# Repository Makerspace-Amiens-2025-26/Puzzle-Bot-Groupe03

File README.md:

# Puzzle Bot

## Description

Puzzle Bot est une machine automatisée capable de détecter, saisir et assembler les pièces d'un puzzle. Le projet combine plusieurs domaines techniques : conception mécanique, électronique, programmation, vision par ordinateur et fabrication numérique.

## Objectifs
* Détecter les pièces d'un puzzle à l'aide d'une caméra.
* Identifier leur position et leur orientation.
* Déplacer les pièces grâce à un système robotisé.
* Assembler automatiquement le puzzle.
## Technologies utilisées
* Arduino
* Python
* OpenCV
* Onshape
* Impression 3D 
* Découpe laser
## Structure du projet 
* /CAO : modèles 3D et plans.
* /Code : programmes de contrôle et de vision.
* /Electronique : schémas et câblage.
* /Documentation : rapports, poster et ressources.
## Équipe
* Moutassi joseph 
* Mbognie Donna
* Fokem bracins
* Antoni calvin
* Andy Metogo
* Elsy Kounda
## Ressources
* Documentation du projet
* Modèle Onshape
* Poster de présentation

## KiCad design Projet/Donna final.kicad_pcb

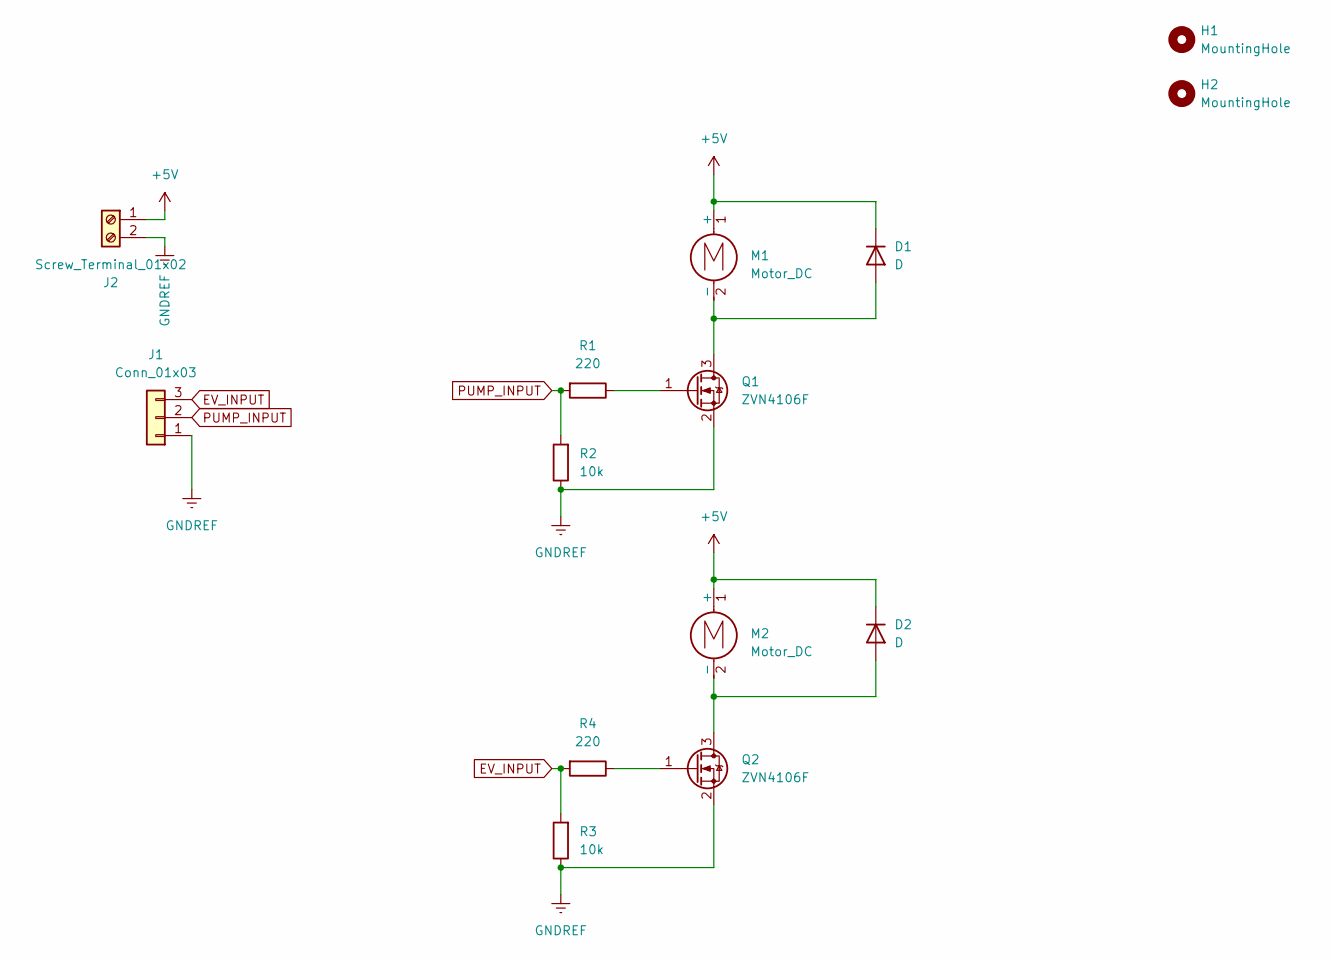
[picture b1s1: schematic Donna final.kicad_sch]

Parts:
D1, D2: D; D_SMA
H1, H2: MountingHole; MountingHole_3.2mm_M3
J1: Conn_01x03; PinHeader_1x03_P2.54mm_Vertical
J2: Screw_Terminal_01x02; TerminalBlock_Phoenix_PT-1,5-2-5.0-H_1x02_P5.00mm_Horizontal
M1, M2: Motor_DC; TerminalBlock_Phoenix_PT-1,5-2-5.0-H_1x02_P5.00mm_Horizontal
Q1, Q2: ZVN4106F; TO-92L_Inline
R1, R4: 220; R_1206_3216Metric_Pad1.30x1.75mm_HandSolder
R2, R3: 10k; R_1206_3216Metric_Pad1.30x1.75mm_HandSolder

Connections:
+5V: D1.1 (K), D2.1 (K), J2.1, M1.1 (+), M2.1 (+)
EV_INPUT: J1.3, R3.2, R4.2
GNDREF: J1.1, J2.2, Q1.2 (S), Q2.2 (S), R2.1, R3.1
unnamed: D1.2 (A), M1.2 (-), Q1.3 (D)
unnamed: D2.2 (A), M2.2 (-), Q2.3 (D)
unnamed: Q1.1 (G), R1.1
unnamed: Q2.1 (G), R4.1
PUMP_INPUT: J1.2, R1.2, R2.2

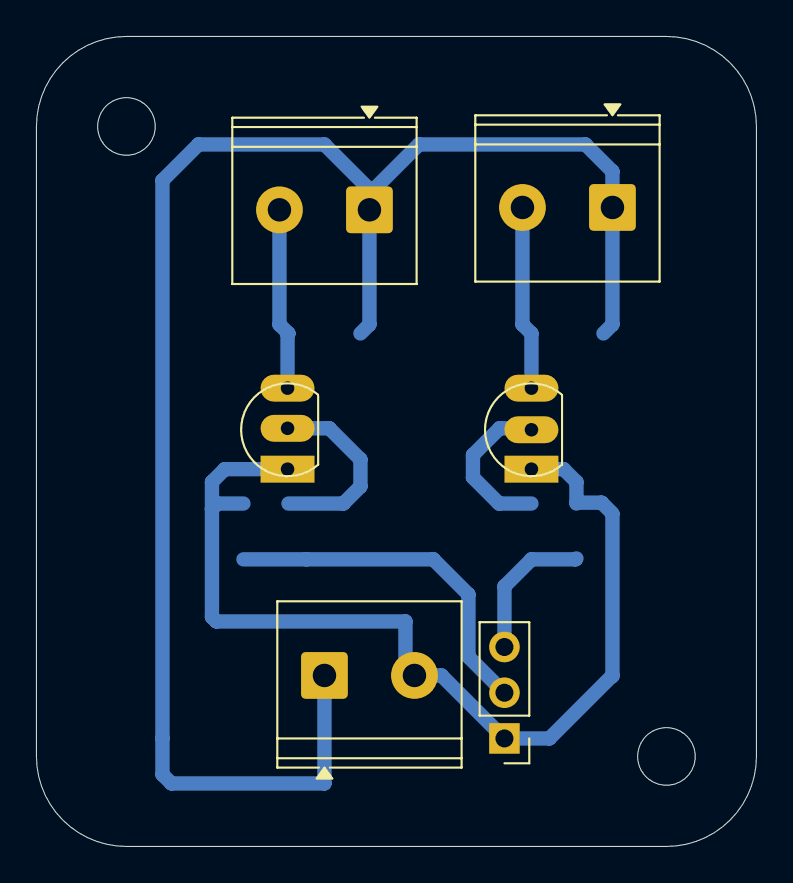
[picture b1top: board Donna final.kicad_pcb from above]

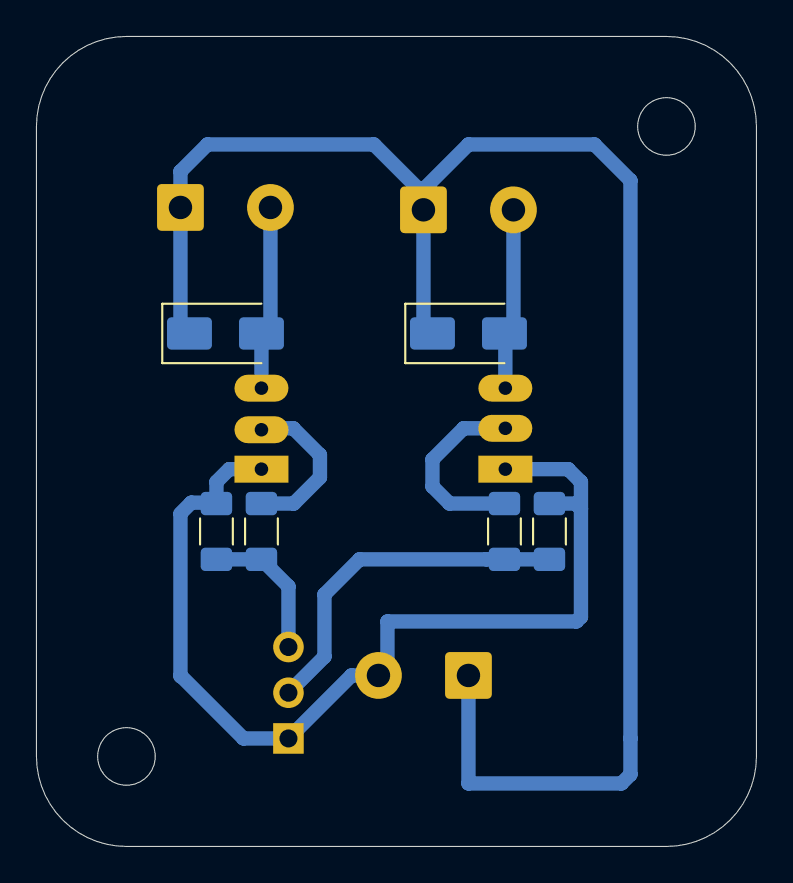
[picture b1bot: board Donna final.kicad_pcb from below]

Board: 2 copper layers, 40.0 x 45.0 mm, 14 parts (6 on the bottom side), 8 nets.

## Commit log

2026-06-03 Poster.png
2026-06-03 Rename docs/images/IMG-20260603-WA0007.jpg to docs/Poster.jpg
2026-06-03 poster groupe 3
2026-06-12 Fix Onshape project link in documentation
    Updated the Onshape project link to a new URL.
2026-06-12 Update Onshape project link in documentation
2026-06-12 Modify project links in documentation
    Updated the project link and added a GitHub repository link.
2026-06-12 Revise project overview and GitHub repository link
    Updated project description and GitHub link in documentation.
2026-06-12 Fix formatting in objectifs.md
    Removed extra space in section headers and updated formatting.
2026-06-12 Update README with project details and team information
    Added project objectives, technologies used, project structure, team members, and resources.
2026-06-12 Update README to reflect Puzzle Bot project
    Removed template project information and updated title.
2026-06-12 Expand project documentation for Puzzle Bot
    Added detailed project specifications for Puzzle Bot, including context, objectives, functional needs, technical constraints, expected performance, safety measures, and deliverables.
2026-06-12 Remove duplicate bullet points in etudes.md
    Duplicate bullet points in the objectives, functional needs, technical constraints, expected performances, safety, and deliverables sections.
2026-06-12 Format README sections with bullet points
    Updated the README to use bullet points for objectives, technologies, project structure, team, and resources.
2026-06-13 Change iframe source and update integration instructions
    Updated iframe source for Onshape project visualization and modified warning message instructions.
2026-06-13 Update poster section to include image
    Replaced poster link with an image in the documentation.
2026-06-13 Rename docs/images/WhatsApp Image 2026-06-13 at 13.27.32 (5).jpeg to Twins Piece.jpeg
2026-06-13 Refine project context in etudes.md
    Removed redundant sentence from project context.
2026-06-13 Revise titles and expand technical choices section
    Updated section titles and added technical choices details.
2026-06-13 Correct section titles in etudes.md
    Updated section titles for consistency and clarity.
2026-06-13 Expand electronics section with technical choices
    Added detailed technical choices for the robot's electronics, including components and their purposes.
2026-06-13 Add images to various sections in etudes.md
2026-06-13 Add additional image and description for camera support
2026-06-13 Add section on mechanical conception
2026-06-13 Fix mermaid diagram and add initialization script
    Updated mermaid diagram syntax and added initialization script for rendering.
2026-06-13 Update mechanical design section in conception.md
    Added mechanical design details and images for the CNC machine.
2026-06-13 rename project/Les ressources du projet.md
2026-06-13 Create Ressources
2026-06-13 Change headers from H1 to H2 in etudes.md
2026-06-13 Update header levels in conception.md
    Change section headers from H1 to H2 for better structure.
2026-06-13 Modify navigation order and add children attribute
    Updated navigation order and added has_children attribute.
2026-06-14 Document project resources and structure
    Added detailed project resources including mechanical design, electronics, programming, and source code sections.
2026-06-14 Add project resources documentation
    Added detailed project resources including sections on mechanical design, electronics, programming, and source code.
2026-06-14 Add image to conception documentation
    Added an image to the documentation for better clarity.
2026-06-14 Update conception.md with Arduino and CNC Shield info
    Added section on Arduino and CNC Shield connection details.
2026-06-14 Update section title to bold format
2026-06-14 Bold the section title for emphasis
2026-06-17 Create Conception électronique
2026-06-17 Add layout and metadata to Conception électronique
2026-06-17 Create Conception mécanique
2026-06-17 Create Programmation
2026-06-17 Update Conception électronique
2026-06-17 Rename Conception électronique to Conception électronique.md
2026-06-17 Add section header for Conception Mecanique
2026-06-17 Fix formatting of Conception électronique header
2026-06-17 Revise conception and prototyping documentation
    This update revises the conception and prototyping sections of the documentation, detailing the design process, prototyping results, and tools used for the Puzzle Bot project.
2026-06-17 Change navigation order and add images
    Updated the navigation order and added images to the document.
2026-06-17 Fix image links and enhance documentation clarity
    Updated image syntax and clarified text regarding the improvements and failures encountered during testing.
2026-06-17 Fix image formatting and update design failure explanation
    Corrected image formatting and clarified design failure.
2026-06-17 Fix image links and enhance documentation clarity
    Corrected image formatting and improved text clarity regarding the testing results and modifications made to the components.
2026-06-17 Revise content and images in results document
    Updated images and corrected text in the document.
2026-06-17 Mettre à jour le document des essais et résultats
    Ajout d'une image et mise à jour des résultats des essais sur les prototypes.
2026-06-17 Revise test results and improvements in documentation
    Updated the document with results and improvements from tests on printed wooden supports. Included images and detailed observations on design failures and enhancements.
2026-06-17 Fix section headers for consistency in document
2026-06-17 Remove empty line in documentation
2026-06-17 Change nav_order from 6 to 5 in documentation
2026-06-17 Update navigation order for fabrication steps
2026-06-17 Revise document to include future perspectives and improvements
    Updated the document to outline future perspectives and improvements for the Puzzle-Bot project, including advancements in AI, mechanical precision, electronic reliability, and software optimization.
